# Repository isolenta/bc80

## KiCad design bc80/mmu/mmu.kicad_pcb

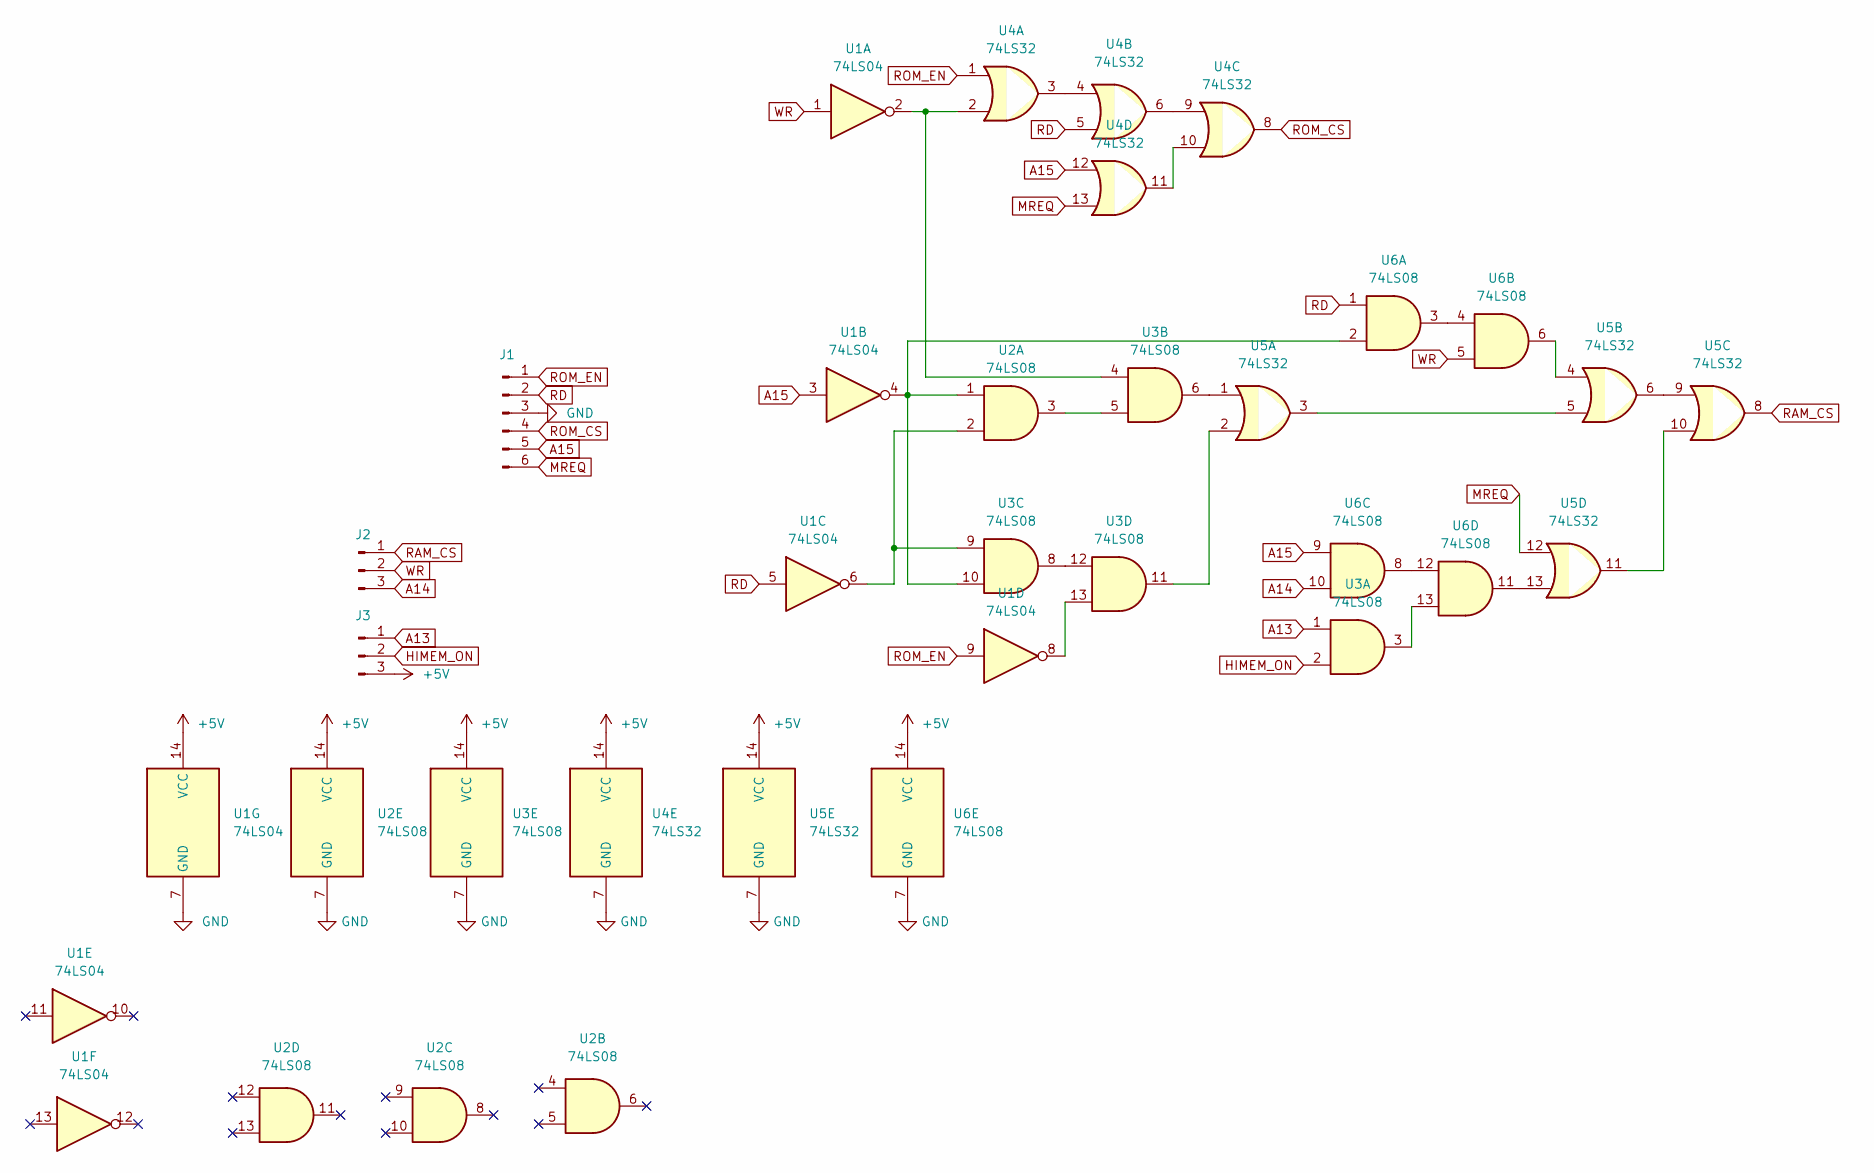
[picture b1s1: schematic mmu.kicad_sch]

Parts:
J1: Conn_01x06_Male; PinHeader_1x06_P2.54mm_Vertical
J2, J3: Conn_01x03_Male; PinHeader_1x03_P2.54mm_Vertical
U1: 74LS04; DIP-14_W7.62mm_LongPads
U2, U3, U6: 74LS08; DIP-14_W7.62mm_LongPads
U4, U5: 74LS32; DIP-14_W7.62mm_LongPads

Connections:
+5V: J3.3, U1.14 (VCC), U2.14 (VCC), U3.14 (VCC), U4.14 (VCC), U5.14 (VCC), U6.14 (VCC)
A13: J3.1, U3.1
A14: J2.3, U6.10
A15: J1.5, U1.3, U4.12, U6.9
GND: J1.3, U1.7 (GND), U2.7 (GND), U3.7 (GND), U4.7 (GND), U5.7 (GND), U6.7 (GND)
HIMEM_ON: J3.2, U3.2
MREQ: J1.6, U4.13, U5.12
unnamed: U1.2, U3.4, U4.2
unnamed: U1.4, U2.1, U3.10, U6.2
unnamed: U1.6, U2.2, U3.9
unnamed: U1.8, U3.13
unnamed: U2.3, U3.5
unnamed: U3.3, U6.13
unnamed: U3.6, U5.1
unnamed: U3.11, U5.2
unnamed: U3.8, U3.12
unnamed: U4.3, U4.4
unnamed: U4.6, U4.9
unnamed: U4.10, U4.11
unnamed: U5.3, U5.5
unnamed: U5.4, U6.6
unnamed: U5.6, U5.9
unnamed: U5.10, U5.11
unnamed: U5.13, U6.11
unnamed: U6.3, U6.4
unnamed: U6.8, U6.12
RAM_CS: J2.1, U5.8
RD: J1.2, U1.5, U4.5, U6.1
ROM_CS: J1.4, U4.8
ROM_EN: J1.1, U1.9, U4.1
WR: J2.2, U1.1, U6.5

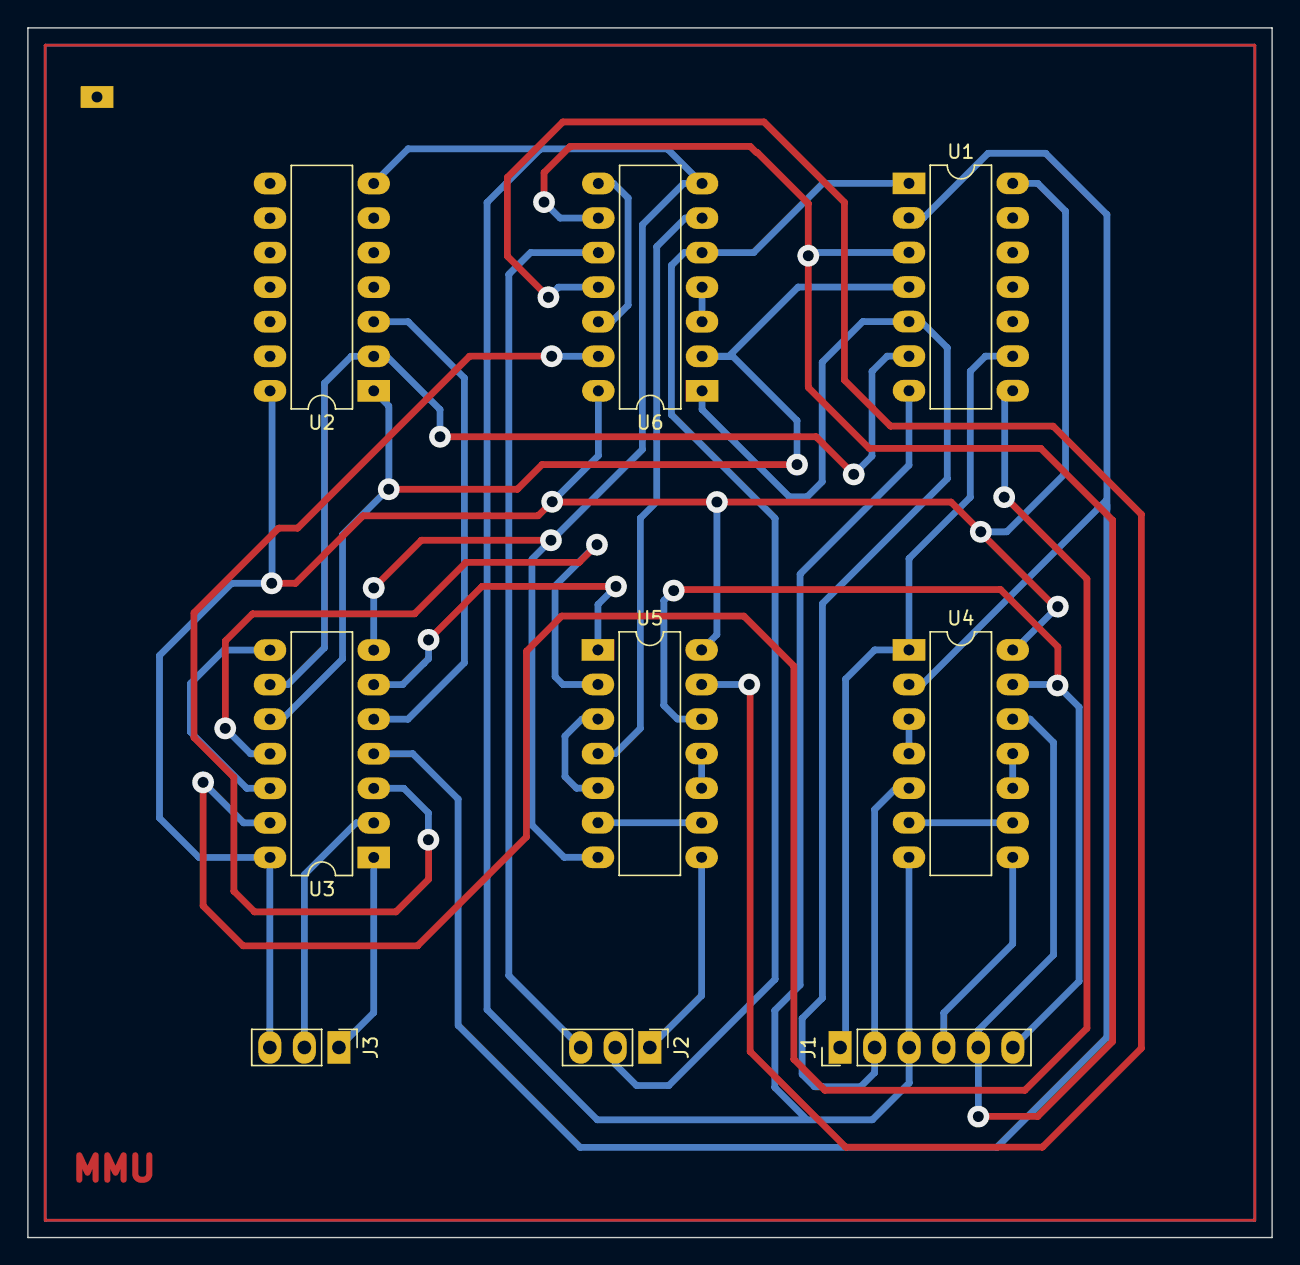
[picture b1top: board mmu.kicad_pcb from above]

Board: 2 copper layers, 91.4 x 88.9 mm, 9 parts (0 on the bottom side), 31 nets.

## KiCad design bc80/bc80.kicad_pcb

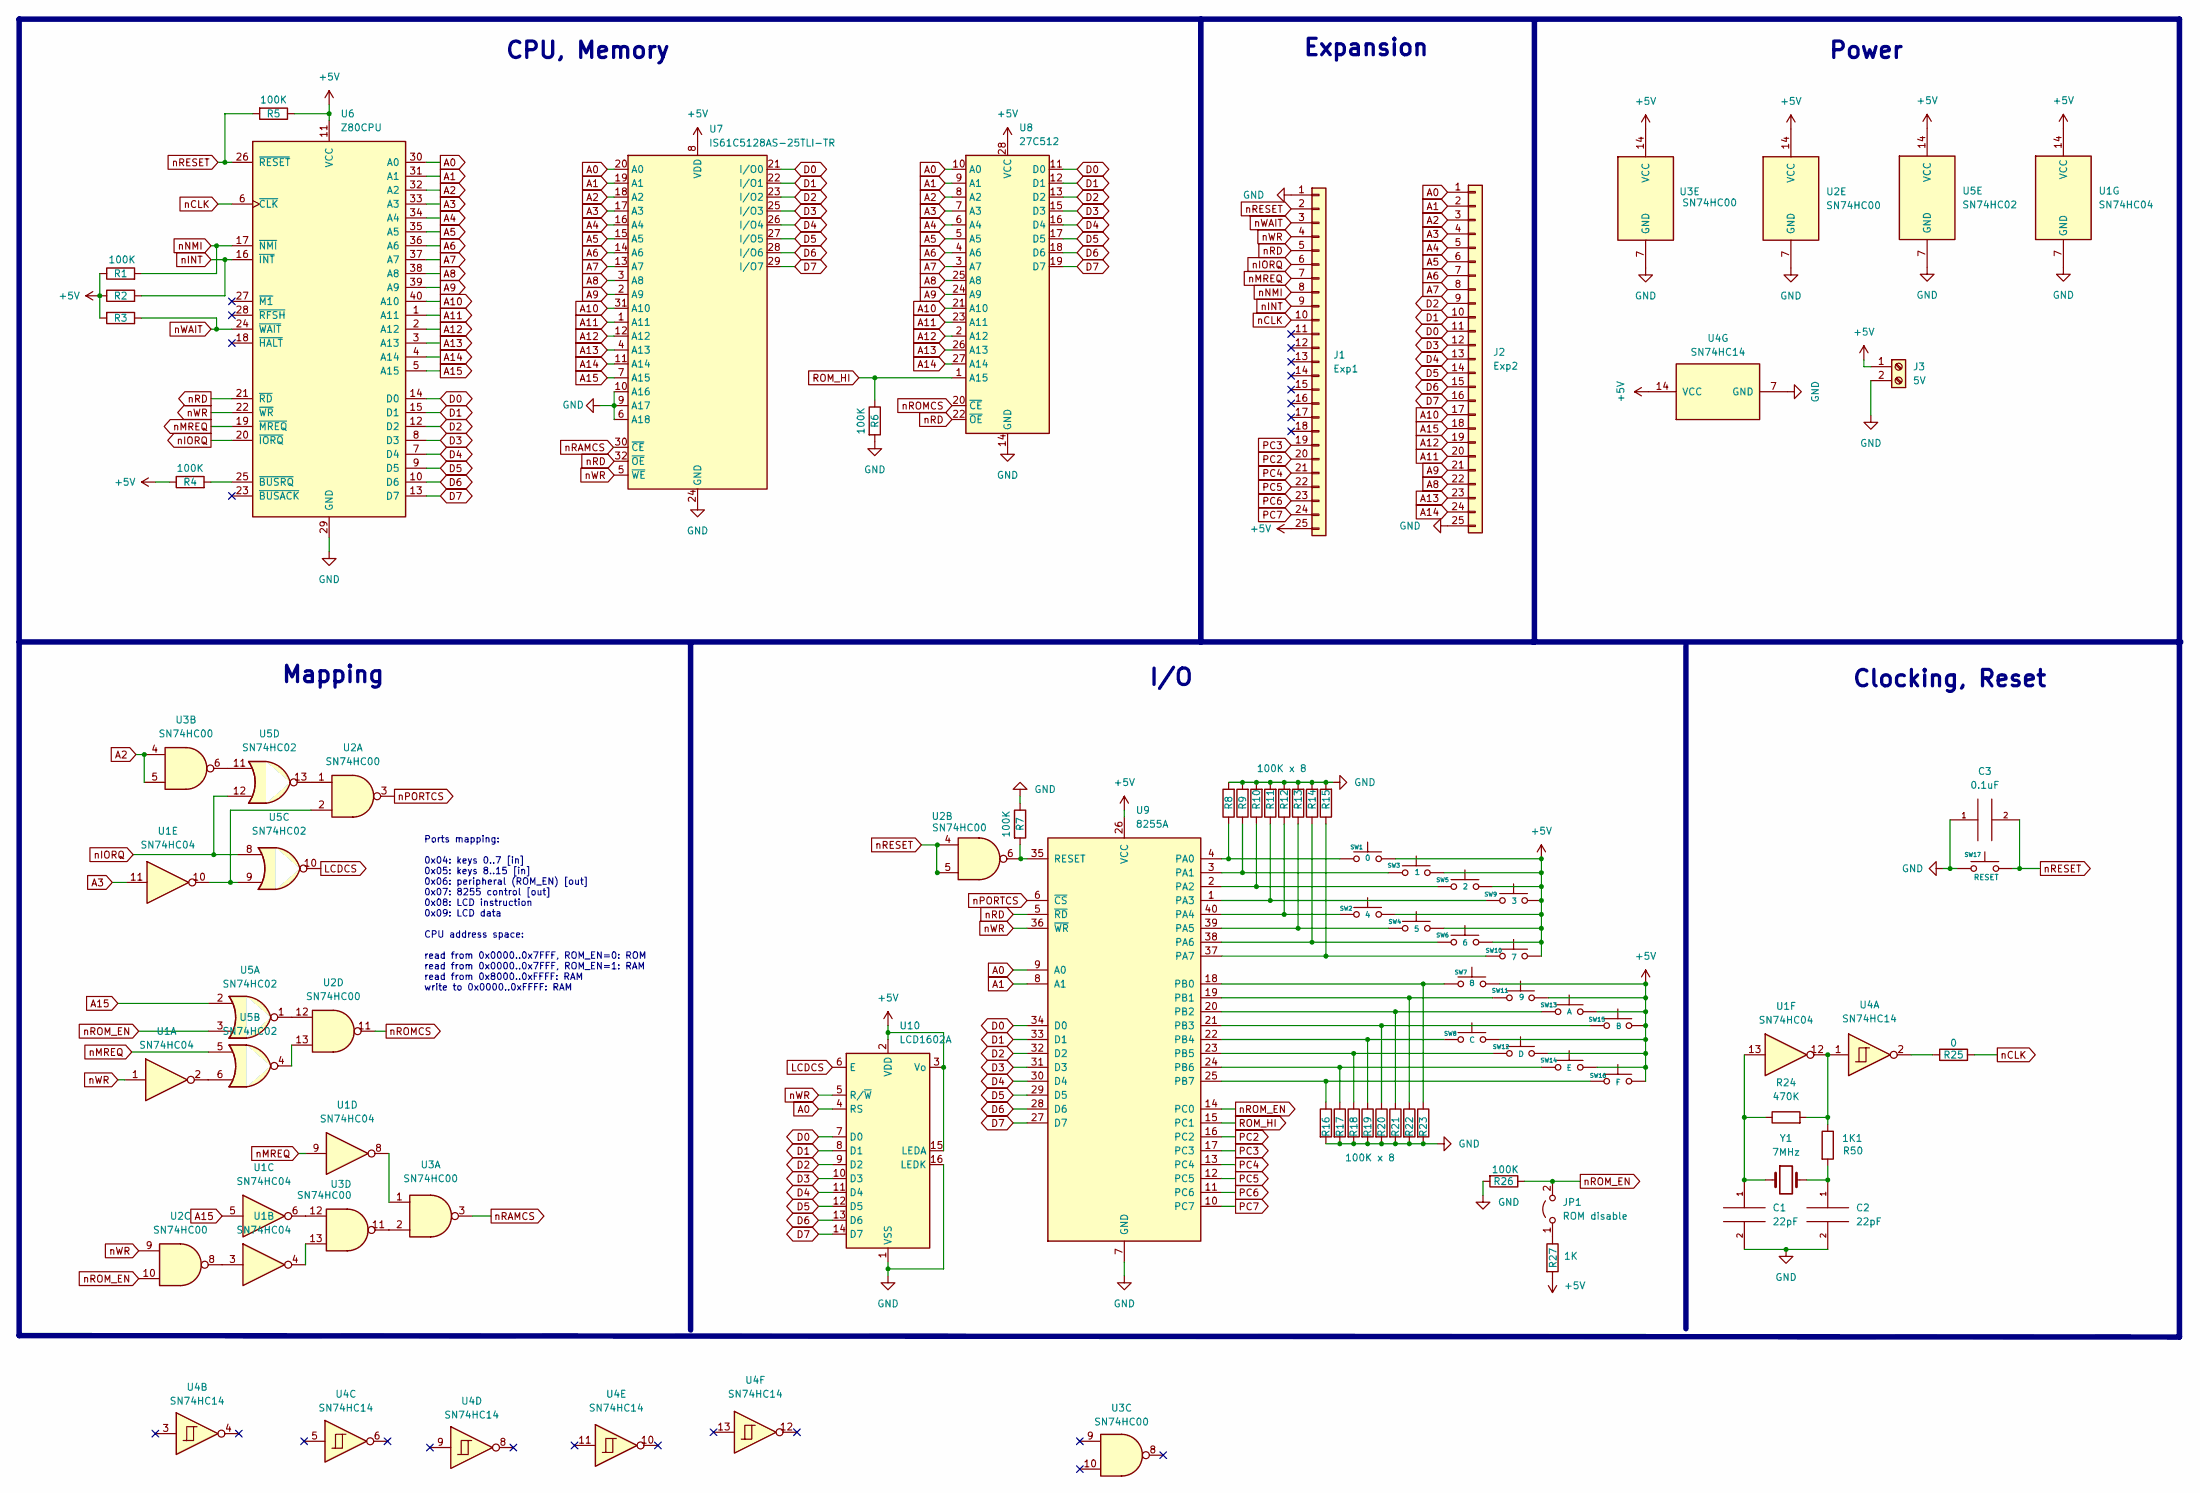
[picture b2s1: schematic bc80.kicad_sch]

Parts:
1K1: R50; R_0805_2012Metric
C1, C2: 22pF; C_0805_2012Metric
C3: 0.1uF; C_0805_2012Metric
J1: Exp1; PinHeader_1x25_P2.54mm_Vertical
J2: Exp2; PinHeader_1x25_P2.54mm_Vertical
J3: 5V; TerminalBlock_Altech_AK300-2_P5.00mm
JP1: ROM disable; PinHeader_1x02_P2.00mm_Vertical
R1, R2, R3, R4, R5, R6, R7, R9, R10, R11, R12, R13, R14, R15, R16, R17, R18, R19, R20, R21, R22, R26: 100K; R_0805_2012Metric
R8, R23: 100K x 8; R_0805_2012Metric
R24: 470K; R_0805_2012Metric
R25: 0; R_0805_2012Metric
R27: 1K; R_0805_2012Metric
SW1: 0; SW_Push_1P1T_NO_6x6mm_H9.5mm
SW2: 4; SW_Push_1P1T_NO_6x6mm_H9.5mm
SW3: 1; SW_Push_1P1T_NO_6x6mm_H9.5mm
SW4: 5; SW_Push_1P1T_NO_6x6mm_H9.5mm
SW5: 2; SW_Push_1P1T_NO_6x6mm_H9.5mm
SW6: 6; SW_Push_1P1T_NO_6x6mm_H9.5mm
SW7: 8; SW_Push_1P1T_NO_6x6mm_H9.5mm
SW8: C; SW_Push_1P1T_NO_6x6mm_H9.5mm
SW9: 3; SW_Push_1P1T_NO_6x6mm_H9.5mm
SW10: 7; SW_Push_1P1T_NO_6x6mm_H9.5mm
SW11: 9; SW_Push_1P1T_NO_6x6mm_H9.5mm
SW12: D; SW_Push_1P1T_NO_6x6mm_H9.5mm
SW13: A; SW_Push_1P1T_NO_6x6mm_H9.5mm
SW14: E; SW_Push_1P1T_NO_6x6mm_H9.5mm
SW15: B; SW_Push_1P1T_NO_6x6mm_H9.5mm
SW16: F; SW_Push_1P1T_NO_6x6mm_H9.5mm
SW17: RESET; SW_Push_1P1T_NO_6x6mm_H9.5mm
U1: SN74HC04; DIP-14_W7.62mm
U2, U3: SN74HC00; DIP-14_W7.62mm
U4: SN74HC14; DIP-14_W7.62mm
U5: SN74HC02; DIP-14_W7.62mm
U6: Z80CPU; DIP-40_W15.24mm
U7: IS61C5128AS-25TLI-TR; TSOP-I-32_18.4x8mm_P0.5mm
U8: 27C512; DIP-28_W15.24mm
U9: 8255A; DIP-40_W15.24mm
U10: LCD1602A; WC1602A
Y1: 7MHz; Crystal_HC49-U_Vertical

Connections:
+5V: J1.25, J3.1, R1.1, R2.1, R3.2, R4.1, R5.1, R27.2, SW1.2, SW2.2, SW3.2, SW4.2, SW5.2, SW6.2, SW7.2, SW8.2, SW9.2, SW10.2, SW11.2, SW12.2, SW13.2, SW14.2, SW15.2, SW16.2, U1.14 (VCC), U2.14 (VCC), U3.14 (VCC), U4.14 (VCC), U5.14 (VCC), U6.11 (VCC), U7.8 (VDD), U8.28 (VCC), U9.26 (VCC), U10.2 (VDD), U10.3 (Vo), U10.15 (LEDA)
A0: J2.1, U6.30 (A0), U7.20 (A0), U8.10 (A0), U9.9 (A0), U10.4 (RS)
A1: J2.2, U6.31 (A1), U7.19 (A1), U8.9 (A1), U9.8 (A1)
A2: J2.3, U3.4, U3.5, U6.32 (A2), U7.18 (A2), U8.8 (A2)
A3: J2.4, U1.11, U6.33 (A3), U7.17 (A3), U8.7 (A3)
A4: J2.5, U6.34 (A4), U7.16 (A4), U8.6 (A4)
A5: J2.6, U6.35 (A5), U7.15 (A5), U8.5 (A5)
A6: J2.7, U6.36 (A6), U7.14 (A6), U8.4 (A6)
A7: J2.8, U6.37 (A7), U7.13 (A7), U8.3 (A7)
A8: J2.22, U6.38 (A8), U7.3 (A8), U8.25 (A8)
A9: J2.21, U6.39 (A9), U7.2 (A9), U8.24 (A9)
A10: J2.17, U6.40 (A10), U7.31 (A10), U8.21 (A10)
A11: J2.20, U6.1 (A11), U7.1 (A11), U8.23 (A11)
A12: J2.19, U6.2 (A12), U7.12 (A12), U8.2 (A12)
A13: J2.23, U6.3 (A13), U7.4 (A13), U8.26 (A13)
A14: J2.24, U6.4 (A14), U7.11 (A14), U8.27 (A14)
A15: J2.18, U1.5, U5.2, U6.5 (A15), U7.7 (A15)
D0: J2.11, U6.14 (D0), U7.21 (I/O0), U8.11 (D0), U9.34 (D0), U10.7 (D0)
D1: J2.10, U6.15 (D1), U7.22 (I/O1), U8.12 (D1), U9.33 (D1), U10.8 (D1)
D2: J2.9, U6.12 (D2), U7.23 (I/O2), U8.13 (D2), U9.32 (D2), U10.9 (D2)
D3: J2.12, U6.8 (D3), U7.25 (I/O3), U8.15 (D3), U9.31 (D3), U10.10 (D3)
D4: J2.13, U6.7 (D4), U7.26 (I/O4), U8.16 (D4), U9.30 (D4), U10.11 (D4)
D5: J2.14, U6.9 (D5), U7.27 (I/O5), U8.17 (D5), U9.29 (D5), U10.12 (D5)
D6: J2.15, U6.10 (D6), U7.28 (I/O6), U8.18 (D6), U9.28 (D6), U10.13 (D6)
D7: J2.16, U6.13 (D7), U7.29 (I/O7), U8.19 (D7), U9.27 (D7), U10.14 (D7)
GND: C1.2, C2.2, C3.1, J1.1, J2.25, J3.2, R6.2, R7.1, R8.2, R9.2, R10.2, R11.2, R12.2, R13.2, R14.2, R15.2, R16.2, R17.2, R18.2, R19.2, R20.2, R21.2, R22.2, R23.2, R26.2, SW17.1, U1.7 (GND), U2.7 (GND), U3.7 (GND), U4.7 (GND), U5.7 (GND), U6.29 (GND), U7.6 (A18), U7.9 (A17), U7.10 (A16), U7.24 (GND), U8.14 (GND), U9.7 (GND), U10.1 (VSS), U10.16 (LEDK)
LCDCS: U5.10, U10.6 (E)
unnamed: 1K1.1, R24.2, U1.12, U4.1
unnamed: 1K1.2, C2.1, Y1.2
unnamed: C1.1, R24.1, U1.13, Y1.1
unnamed 30: JP1.1 (A), R27.1; also elsewhere on the board
unnamed: R4.2, U6.25 (~BUSRQ)
unnamed: R7.2, U2.6, U9.35 (RESET)
unnamed: R8.1, SW1.1, U9.4 (PA0)
unnamed: R9.1, SW3.1, U9.3 (PA1)
unnamed: R10.1, SW5.1, U9.2 (PA2)
unnamed: R11.1, SW9.1, U9.1 (PA3)
unnamed: R12.1, SW2.1, U9.40 (PA4)
unnamed: R13.1, SW4.1, U9.39 (PA5)
unnamed: R14.1, SW6.1, U9.38 (PA6)
unnamed: R15.1, SW10.1, U9.37 (PA7)
unnamed: R16.1, SW16.1, U9.25 (PB7)
unnamed: R17.1, SW14.1, U9.24 (PB6)
unnamed: R18.1, SW12.1, U9.23 (PB5)
unnamed: R19.1, SW8.1, U9.22 (PB4)
unnamed: R20.1, SW15.1, U9.21 (PB3)
unnamed: R21.1, SW13.1, U9.20 (PB2)
unnamed: R22.1, SW11.1, U9.19 (PB1)
unnamed: R23.1, SW7.1, U9.18 (PB0)
unnamed: R25.1, U4.2
unnamed: U1.2, U5.6
unnamed: U1.3, U2.8
unnamed: U1.4, U3.13
unnamed: U1.6, U3.12
unnamed: U1.8, U3.1
unnamed: U1.10, U2.2, U5.9
unnamed: U2.1, U5.13
unnamed: U2.12, U5.1
unnamed: U2.13, U5.4
unnamed: U3.6, U5.11
unnamed: U3.2, U3.11
PC2: J1.20, U9.16 (PC2)
PC3: J1.19, U9.17 (PC3)
PC4: J1.21, U9.13 (PC4)
PC5: J1.22, U9.12 (PC5)
PC6: J1.23, U9.11 (PC6)
PC7: J1.24, U9.10 (PC7)
ROM_HI: R6.1, U8.1 (A15), U9.15 (PC1)
nCLK: J1.10, R25.2, U6.6 (~CLK)
nINT: J1.9, R2.2, U6.16 (~INT)
nIORQ: J1.6, U5.8, U5.12, U6.20 (~IORQ)
nMREQ: J1.7, U1.9, U5.5, U6.19 (~MREQ)
nNMI: J1.8, R1.2, U6.17 (~NMI)
nPORTCS: U2.3, U9.6 (~CS)
nRAMCS: U3.3, U7.30 (~CE)
nRD: J1.5, U6.21 (~RD), U7.32 (~OE), U8.22 (~OE), U9.5 (~RD)
nRESET: C3.2, J1.2, R5.2, SW17.2, U6.26 (~RESET)
nROMCS: U2.11, U8.20 (~CE)
nROM_EN: JP1.2 (B), R26.1, U2.10, U5.3, U9.14 (PC0); also elsewhere on the board
nWAIT: J1.3, R3.1, U6.24 (~WAIT)
nWR: J1.4, U1.1, U2.9, U6.22 (~WR), U7.5 (~WE), U9.36 (~WR), U10.5 (R/~W)

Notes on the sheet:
Mapping
Expansion
I/O
Clocking, Reset
Power
CPU, Memory
Ports mapping: 0x04: keys 0..7 [in] 0x05: keys 8..15 [in] 0x06: peripheral (ROM_EN) [out] 0x07: 8255 control [out] 0x08: LCD instruction 0x09: LCD data CPU address space: read from 0x0000..0x7FFF, ROM_EN=0: ROM read from 0x0000..0x7FFF, ROM_EN=1: RAM read from 0x8000..0xFFFF: RAM write to 0x0000..0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

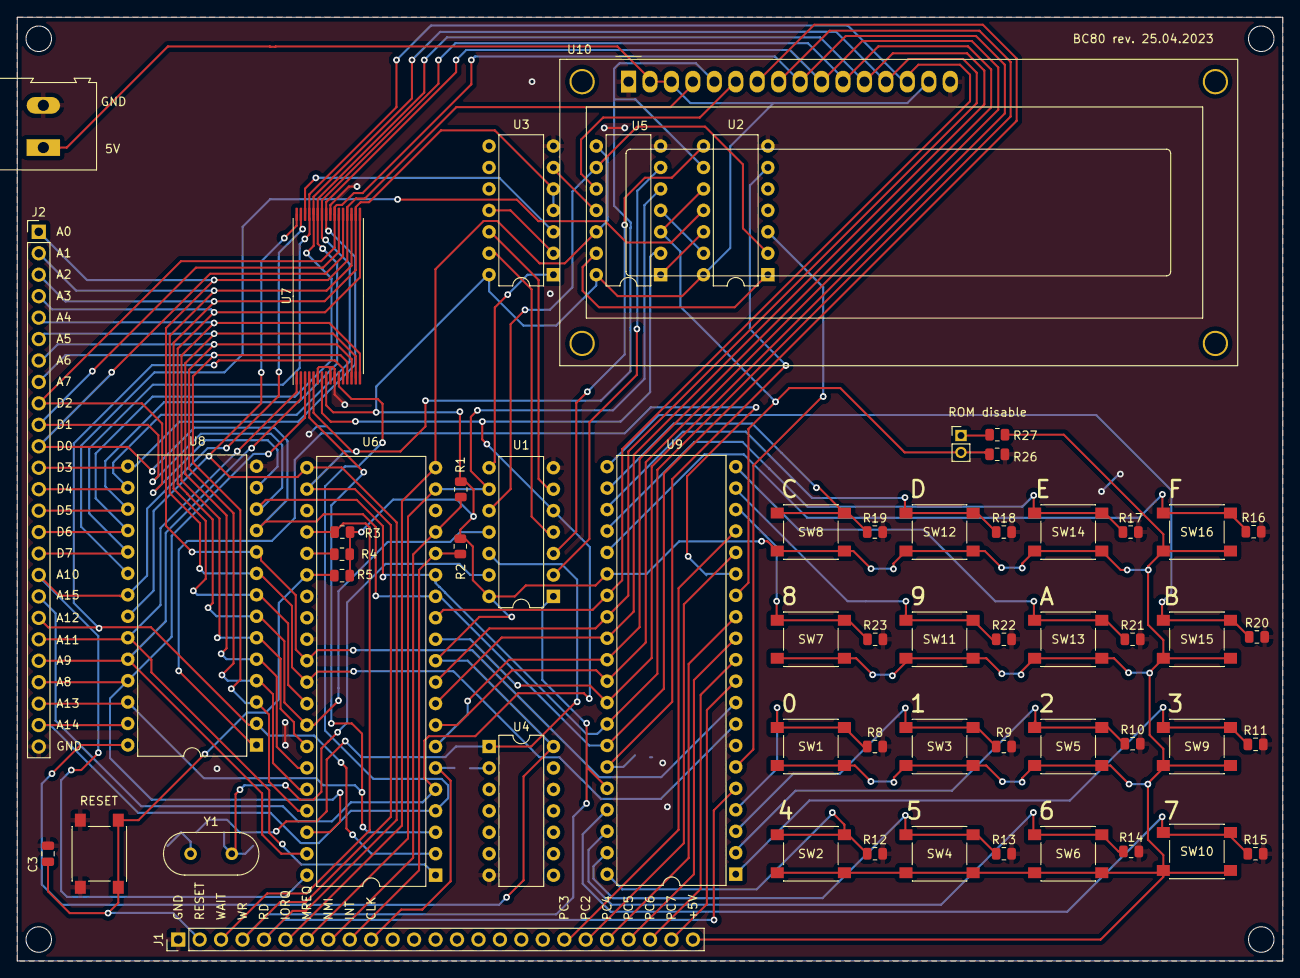
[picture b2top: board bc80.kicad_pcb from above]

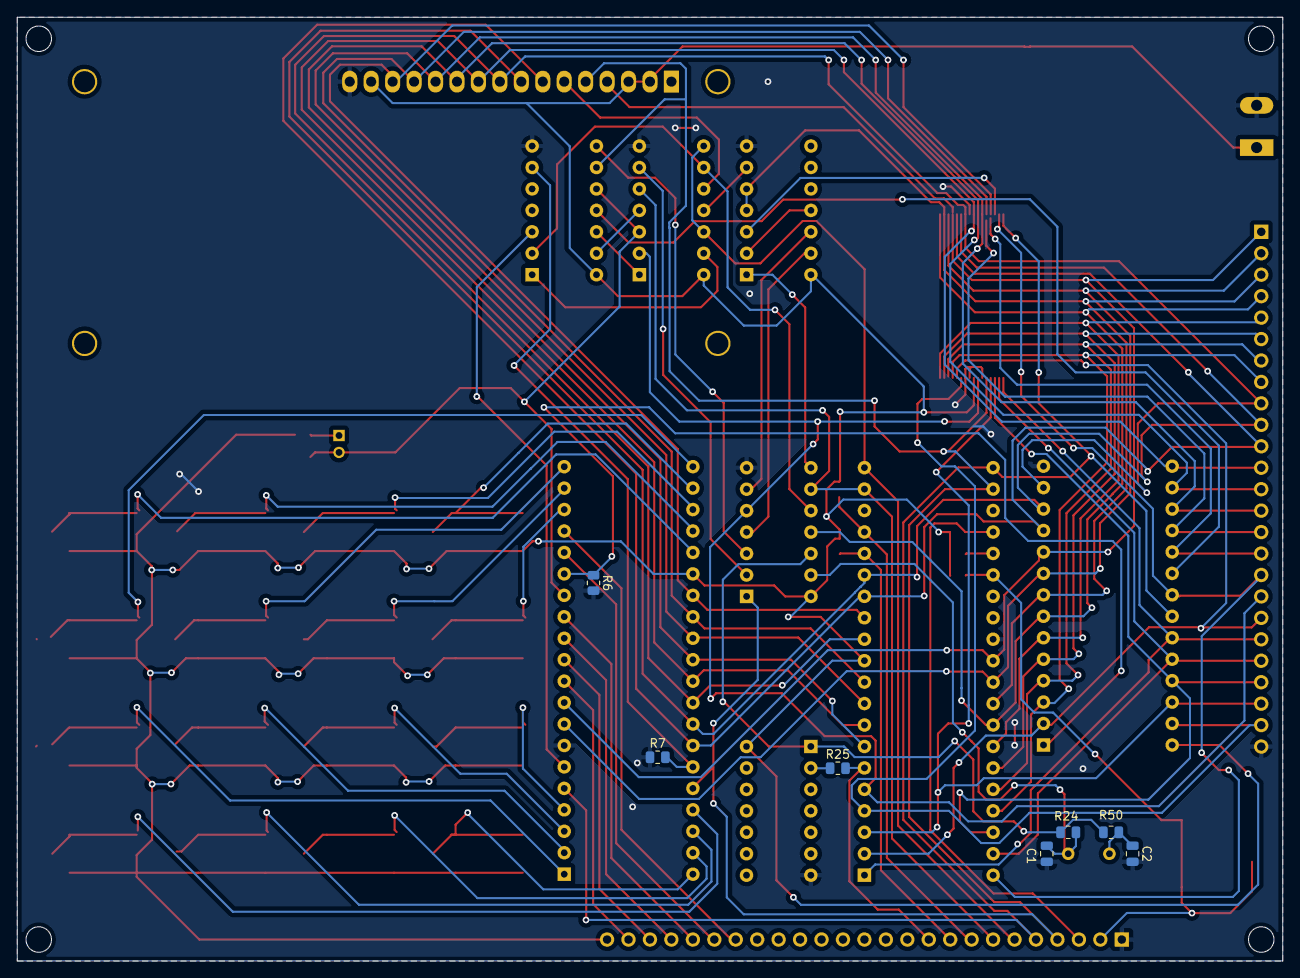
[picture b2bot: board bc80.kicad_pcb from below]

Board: 2 copper layers, 149.9 x 111.8 mm, 63 parts (7 on the bottom side), 81 nets.

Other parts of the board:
ROM disable: ROM disable; PinHeader_1x02_P2.00mm_Vertical

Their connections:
unnamed 30: ROM disable.1 (A); also elsewhere on the board
nROM_EN: ROM disable.2 (B); also elsewhere on the board

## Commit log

2023-06-14 add debugger files
2023-06-14 add 3rd party docs
2023-06-14 add as/disas sources
2023-06-14 add gitignore
2023-06-14 add kicad projects
2023-06-18 introduce multiple sections support start implementing ELF target backend
2023-06-19 implement ELF target backend and on the fly section switching
2023-06-21 fix instruction encoding for relative jumps
2023-06-21 resolve forward constants for DEF directives
2023-06-21 fix LD with immediate address destination
2023-06-22 add tests
2023-06-22 remove support of undocumented instructions
2023-06-22 fix BIT with (I+D) argument
2023-06-22 a few encode/decode fixes
2023-06-24 add test for relative jumps and fix encoding errors
2023-06-24 add tests for include, def, incbin
2023-06-24 add tests for expressions, fix expression evaluator
2023-06-24 wrap assembler/disassembler into library with stateless API
2023-06-24 support for expressions: % (mod), << (shl), >> (shr)
2023-06-24 fix grammar warnings
2023-06-25 fix bug with terminating zero
2023-06-28 introduce allocations manager with profiler; deallocate dangling allocations at teardown; hashmap refactoring
2023-06-29 remove excess warning
2023-07-02 project directory and build system refactoring start working on c preprocessor
2023-08-08 a few fixes in MMU schematics and layout
2023-08-08 start implementing (reduced) c preprocessor
2023-08-08 add bluepill application for MMU board debugging
2024-02-15 as: better error reporing
2024-12-26 as: implemented local labels
2024-12-28 as: support SNA target format
2024-12-28 as: support of REPT..ENDR macro
2025-01-06 preproc: reset/rethink project
2025-01-06 cleanup
2025-01-06 bluepill debugger changes
2025-01-06 add initial sysmon for bc80
2025-01-07 project refactoring
2025-01-12 rcc: introduce preprocessor stage
2025-01-18 rcc: parse preprocessed source and build parse tree
2025-01-18 rcc: add bool type to parser
2025-01-19 rcc: fix preprocessor issues
2025-01-20 rcc: add column position to diagnostics
2025-01-22 rcc: generic error reporting
2025-01-23 rcc: fix column position
2025-01-24 rcc: handsome error messages
2025-01-26 rcc: start implementing semantics analysis: capture global declarations
2025-01-29 compiler: use cmake for building
2025-02-16 disas: print num cycles per instruction
2025-02-16 compiler: fix buffer overrun
2025-02-16 as: add 'profile..endprofile' directives for per block cycles/bytes counting
2025-02-16 bluepill debugger: update protocol and better ux
2025-02-16 remove obsolete files
2025-02-18 as: fancy error messages
2025-02-18 as: fix recursive compile-time expression
2025-02-18 as: add column number to diagnostic messages
2025-02-18 as: fix typo
2025-02-18 compiler: fix cmake dependencies
2025-02-28 compiler: support undocumented z80 opcodes with ixl, ixh, iyl, iyh
2025-03-01 as: use '=' as alias for EQU
2025-03-01 as: autoprofile code/data blocks
2025-03-01 compiler: fix buffer overruns
2025-03-01 as: code refactoring
2025-03-01 as: expose counter variable in REPT block; variables refactoring
2025-03-02 as: improve section directive syntax and processing
2025-03-02 as: support expression as REPT argument
2025-03-06 as: add integer overflow sanity checks and better diagnostics
2025-03-06 as: multiline c-style comments
2025-03-08 as: refactor expressions and add missed files
2025-03-08 as: nested REPT blocks, bug fixes in expressions evaluation
2025-03-08 as: add IF..ELSE..ENDIF statements
2025-03-08 as: fix expressions issues, refactoring
2025-03-09 as: more refactoring
2025-03-09 compiler: hashmap access methods refactoring
2025-03-09 as: fix integer overflow warning for negative integers
2025-03-29 asm: project refactoring. Canceling rc compiler development; bc80asm/bc80dasm is first class project now.
